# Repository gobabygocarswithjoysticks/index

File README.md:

# Go Baby Go Cars With Joysticks

# Links to instructions and software for [Go Baby Go](https://health.oregonstate.edu/gobabygo) inspired ride on cars modified to have joystick control.

# Instructions

## aosom jeep: 
[https://www.instructables.com/GoBabyGo-Make-a-Joystick-controlled-Ride-on-Car/](https://www.instructables.com/GoBabyGo-Make-a-Joystick-controlled-Ride-on-Car/)
([SERT FRC#2521](https://www.sert2521.org/) & GoBabyGoCarsWithJoysticks)

## firetruck: 
[https://drive.google.com/drive/folders/0B2HJnUrZAwYremFIYW55LVZ2TUU?resourcekey=0-zuVXEhaKQ2dVb-dyiEhITQ](https://drive.google.com/drive/folders/0B2HJnUrZAwYremFIYW55LVZ2TUU?resourcekey=0-zuVXEhaKQ2dVb-dyiEhITQ) 
([SERT FRC#2521](https://www.sert2521.org/) & GoBabyGoCarsWithJoysticks)

## generalized circuit diagram: 
[https://docs.google.com/drawings/d/1BKDrhKLFc0Y3o9NzUfYC5lIbI_fWCTx9kLZsG5Ts-0o/view](https://docs.google.com/drawings/d/1BKDrhKLFc0Y3o9NzUfYC5lIbI_fWCTx9kLZsG5Ts-0o/view)
(GoBabyGoCarsWithJoysticks)

## general instructions for using a GBG-PCB
[https://gobabygocarswithjoysticks.github.io/gbg-pcb/instructions/instructions](https://gobabygocarswithjoysticks.github.io/gbg-pcb/instructions/instructions)
(GoBabyGoCarsWithJoysticks)

## aosom jeep GBG-PCB edition
[https://gobabygocarswithjoysticks.github.io/gbg-pcb/instructions/car-specific/aosom-038-jeep/instructions](https://gobabygocarswithjoysticks.github.io/gbg-pcb/instructions/car-specific/aosom-038-jeep/instructions)
(GoBabyGoCarsWithJoysticks)

## zupapa bumper car GBG-PCB edition
[https://gobabygocarswithjoysticks.github.io/gbg-pcb/instructions/car-specific/zupapa-bumper-car/instructions](https://gobabygocarswithjoysticks.github.io/gbg-pcb/instructions/car-specific/zupapa-bumper-car/instructions)
(GoBabyGoCarsWithJoysticks)

## flybar bumper car GBG-PCB edition
[https://gobabygocarswithjoysticks.github.io/gbg-pcb/instructions/car-specific/flybar-bumper-car/instructions](https://gobabygocarswithjoysticks.github.io/gbg-pcb/instructions/car-specific/flybar-bumper-car/instructions)
(GoBabyGoCarsWithJoysticks)

# Questions or comments?
### Please post [here](https://github.com/gobabygocarswithjoysticks/index/discussions/categories/support-and-troubleshooting) or email us at gobabygocarswithjoysticks@gmail.com

# Software

## web programmer: [https://gobabygocarswithjoysticks.github.io/programmer/](https://gobabygocarswithjoysticks.github.io/programmer/)

### new car code (uploaded by web programmer): [https://github.com/gobabygocarswithjoysticks/car-code](https://github.com/gobabygocarswithjoysticks/car-code)

### [Instructions and Guides for Remote Control](https://github.com/gobabygocarswithjoysticks/car-code/tree/main/rcdocs)

### old code: [https://github.com/gobabygocarswithjoysticks/classic](https://github.com/gobabygocarswithjoysticks/classic)

# CAD

## [Joystick Balls](https://github.com/gobabygocarswithjoysticks/index/tree/main/joystick-balls) (handle)

* [Large](https://github.com/gobabygocarswithjoysticks/index/raw/main/joystick-balls/ball-large.stl)
 
* [Medium](https://github.com/gobabygocarswithjoysticks/index/raw/main/joystick-balls/ball-medium.stl)

* [Small](https://github.com/gobabygocarswithjoysticks/index/raw/main/joystick-balls/ball-small.stl)

[Onshape](https://cad.onshape.com/documents/0606b7a44a156562463230b4/w/c157c0319d8b261b7ab62dff/e/5374dfde2b557ee7c8b2d179) (make a copy of the model to make custom sizes!)

## [Joystick Holder](https://github.com/gobabygocarswithjoysticks/index/tree/main/joystick-holder)

* [Bottom](https://github.com/gobabygocarswithjoysticks/index/raw/main/joystick-holder/joy-holder-bottom.stl)

* [Lid](https://github.com/gobabygocarswithjoysticks/index/raw/main/joystick-holder/joy-holder-lid.stl)

* [Clamp](https://github.com/gobabygocarswithjoysticks/index/raw/main/joystick-holder/joy-holder-clamp.stl)

* [Clip](https://github.com/gobabygocarswithjoysticks/index/raw/main/joystick-holder/joy-holder-clip.stl) (optional, limits joystick to forwards and backwards only)

[Onshape](https://cad.onshape.com/documents/b635ac829ab39856feba8a99/w/07b70b7662805e9b51c5965c/e/4f736c40741061401f9fab29)

assemble with [these screws](https://www.mcmaster.com/95893A174/)

## [PVC Tees](https://github.com/gobabygocarswithjoysticks/index/tree/main/pvc-tee)

[PVC Saddle Tee part 1](https://github.com/gobabygocarswithjoysticks/index/raw/main/pvc-tee/saddle-tee-part-1.stl)

[PVC Saddle Tee part 2](https://github.com/gobabygocarswithjoysticks/index/raw/main/pvc-tee/saddle-tee-part-2.stl)

assemble with [these screws](https://www.mcmaster.com/95893A174/)

Combine with a 1/4-20 nut and a 3/4" long 1/4-20 bolt.

For easier adjustments, use a hex-head bolt and glue it to this [handwheel](https://github.com/gobabygocarswithjoysticks/index/blob/main/pvc-tee/1-4-20%20handwheel.stl)

## Joystick holder for adjustable arms

Add a heatset insert to give this a threaded connection [https://www.mcmaster.com/93365A160/](https://www.mcmaster.com/93365A160/)

Connect this joystick holder to the end of an adjustible arm (like for photography or holding a machinist's dial indicator)

This method of connecting a joystick works well for "bumper-car" style cars.

* [Bottom](https://github.com/gobabygocarswithjoysticks/index/raw/main/joystick-holder/joy-hold-bottom-heatset.stl)

* [Lid](https://github.com/gobabygocarswithjoysticks/index/raw/main/joystick-holder/joy-holder-lid.stl)

* [Clamp](https://github.com/gobabygocarswithjoysticks/index/raw/main/joystick-holder/joy-holder-clamp.stl)

* [Clip](https://github.com/gobabygocarswithjoysticks/index/raw/main/joystick-holder/joy-holder-clip.stl) (optional, limits joystick to forwards and backwards only)

## [Adjustable arms for putting buttons on the headrest](https://github.com/gobabygocarswithjoysticks/index/tree/main/headrest-button-holder)

## [button tray](https://github.com/gobabygocarswithjoysticks/index/tree/main/button-tray)

# GBG-PCB
## [A circuit board for making joystick cars without any soldering](https://github.com/gobabygocarswithjoysticks/gbg-pcb)

### [Instructions for making a GBG-PCB](https://gobabygocarswithjoysticks.github.io/gbg-pcb/instructions/how-to-make-boards)

# Photos

## [firetruck](https://drive.google.com/drive/folders/0B2HJnUrZAwYremFIYW55LVZ2TUU?resourcekey=0-zuVXEhaKQ2dVb-dyiEhITQ)

## [jeep](https://www.instructables.com/GoBabyGo-Make-a-Joystick-controlled-Ride-on-Car/)

---
This webpage is on github here: [https://github.com/gobabygocarswithjoysticks/index](https://github.com/gobabygocarswithjoysticks/index)

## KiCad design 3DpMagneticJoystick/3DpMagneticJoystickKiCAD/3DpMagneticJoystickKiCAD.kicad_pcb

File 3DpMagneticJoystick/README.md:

# 3D Printed Magnetic Joystick

# Components
## 3D Printed
https://cad.onshape.com/documents/d41011462214e930d752a262/w/b2bf284cefb7d2b98141c36b/e/57aa460e157dfdb3f4c097a9
### lid
### ball top
### ball bottom
### spring
### base
Or, skip this and print the alternate base instead if you want to clamp the joystick to a 3/4" PVC pipe.
### (optional) for mounting the joystick to a 3/4" PVC pipe
alternate base

clamp
## Hardware
### 0.313" diameter magnet
[Radial Magnets 8160](https://www.digikey.com/en/products/detail/radial-magnets-inc/8160/5400480)
### 30mm M3 bolt
### M3 nut

### Hardware for clamp mode
2x ??? bolts

2x ??? nuts

??x?? piece of rubber gasket

## Electrical components
#### Screw Terminal
[OSTVN04A150](https://www.digikey.com/en/products/detail/on-shore-technology-inc/OSTVN04A150/1588864)
#### magnet sensors, quantity: 2
[DRV5053OAQLPG](https://www.digikey.com/en/products/detail/texas-instruments/DRV5053OAQLPG/5031909)

## PCB
[PCB]()
Send this zipped folder of gerber files to a PCB manufacturer to have the PCB made. Or, use the links below to order the PCBs.
[OSH Park]()
[PCBWay]()

## Tools
* soldering iron
* solder wire
* small flathead screwdriver
* wire cutters/flush cutters

# Assembly Instructions

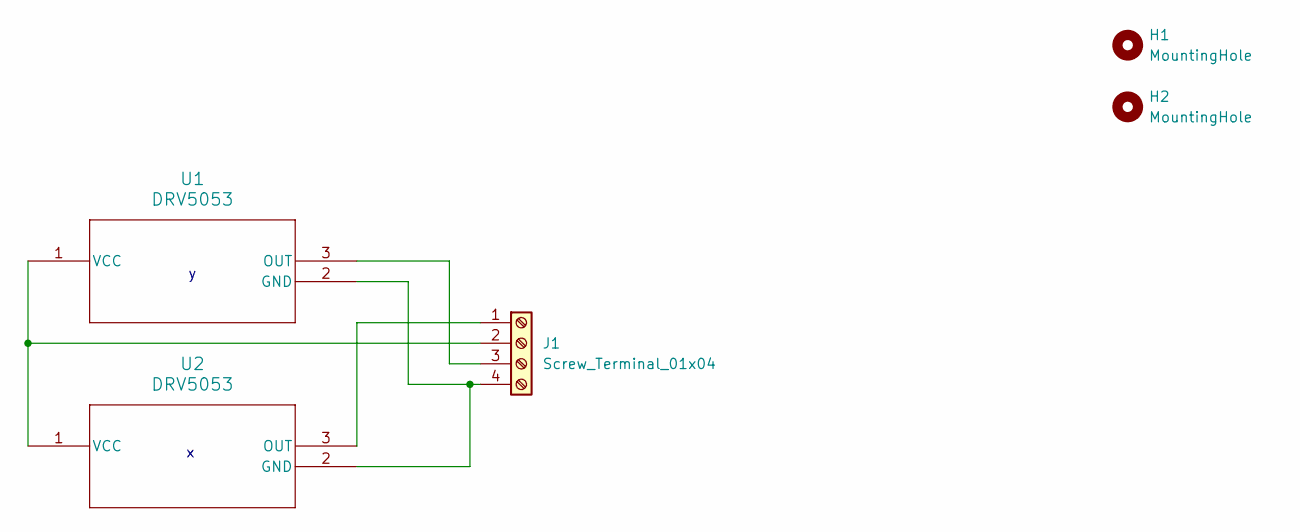
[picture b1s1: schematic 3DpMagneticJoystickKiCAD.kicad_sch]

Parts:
H1, H2: MountingHole; MountingHole_2.2mm_M2_DIN965
J1: Screw_Terminal_01x04; CONN_OSTVN04A150_OST
U1, U2: DRV5053; LPG3_TEX

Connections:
unnamed: J1.1, U2.3 (OUT)
unnamed: J1.2, U1.1 (VCC), U2.1 (VCC)
unnamed: J1.3, U1.3 (OUT)
unnamed: J1.4, U1.2 (GND), U2.2 (GND)

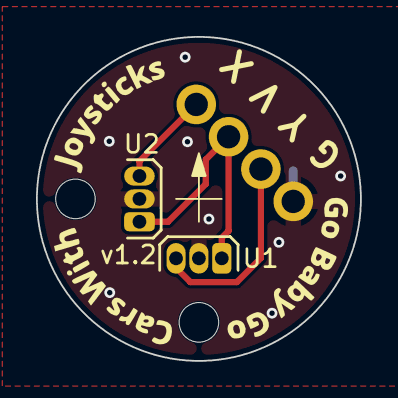
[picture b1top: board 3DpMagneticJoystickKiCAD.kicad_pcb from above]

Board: 2 copper layers, 18.0 x 18.0 mm, 5 parts (1 on the bottom side), 4 nets.

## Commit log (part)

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2023-01-10 add pictures
2023-01-15 upload cad
2023-01-22 rotate parts upright
2024-06-30 update files
2024-06-30 update stls
2024-06-30 add saddle tees
2024-06-30 Rename screw saddle tee part 1.stl to screwsaddleteepart1.stl
2024-06-30 organize files
2024-06-30 upload new pvc tees
2024-07-30 update pvc tees
2024-07-31 update joystick holder STLs
2024-08-20 update slots for nuts
2024-08-20 update orientation
2024-12-30 Update README.md instructable no longer out of date
2025-07-09 add threaded insert STLs, and fix error in ball-large
2025-09-15 edit dimensions of hole
2026-05-05 add heatset holder
